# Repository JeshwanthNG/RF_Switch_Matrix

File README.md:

# RF_Switch_Matrix
Project Implementing RF Switch Matrix, Includes hardware, software and PC application 

## Getting Started

### Prerequisites

- **Windows** for GUI development
- **Visual Studio 2022** with .NET desktop development workload
- **STM32CubeIDE** or **STM32CubeMX** with preferred IDE
- **STM32F439ZI** development board

### Clone the repository

```bash
git clone https://github.com/JeshwanthNG/RF_Switch_Matrix.git
cd RF_Switch_Matrix

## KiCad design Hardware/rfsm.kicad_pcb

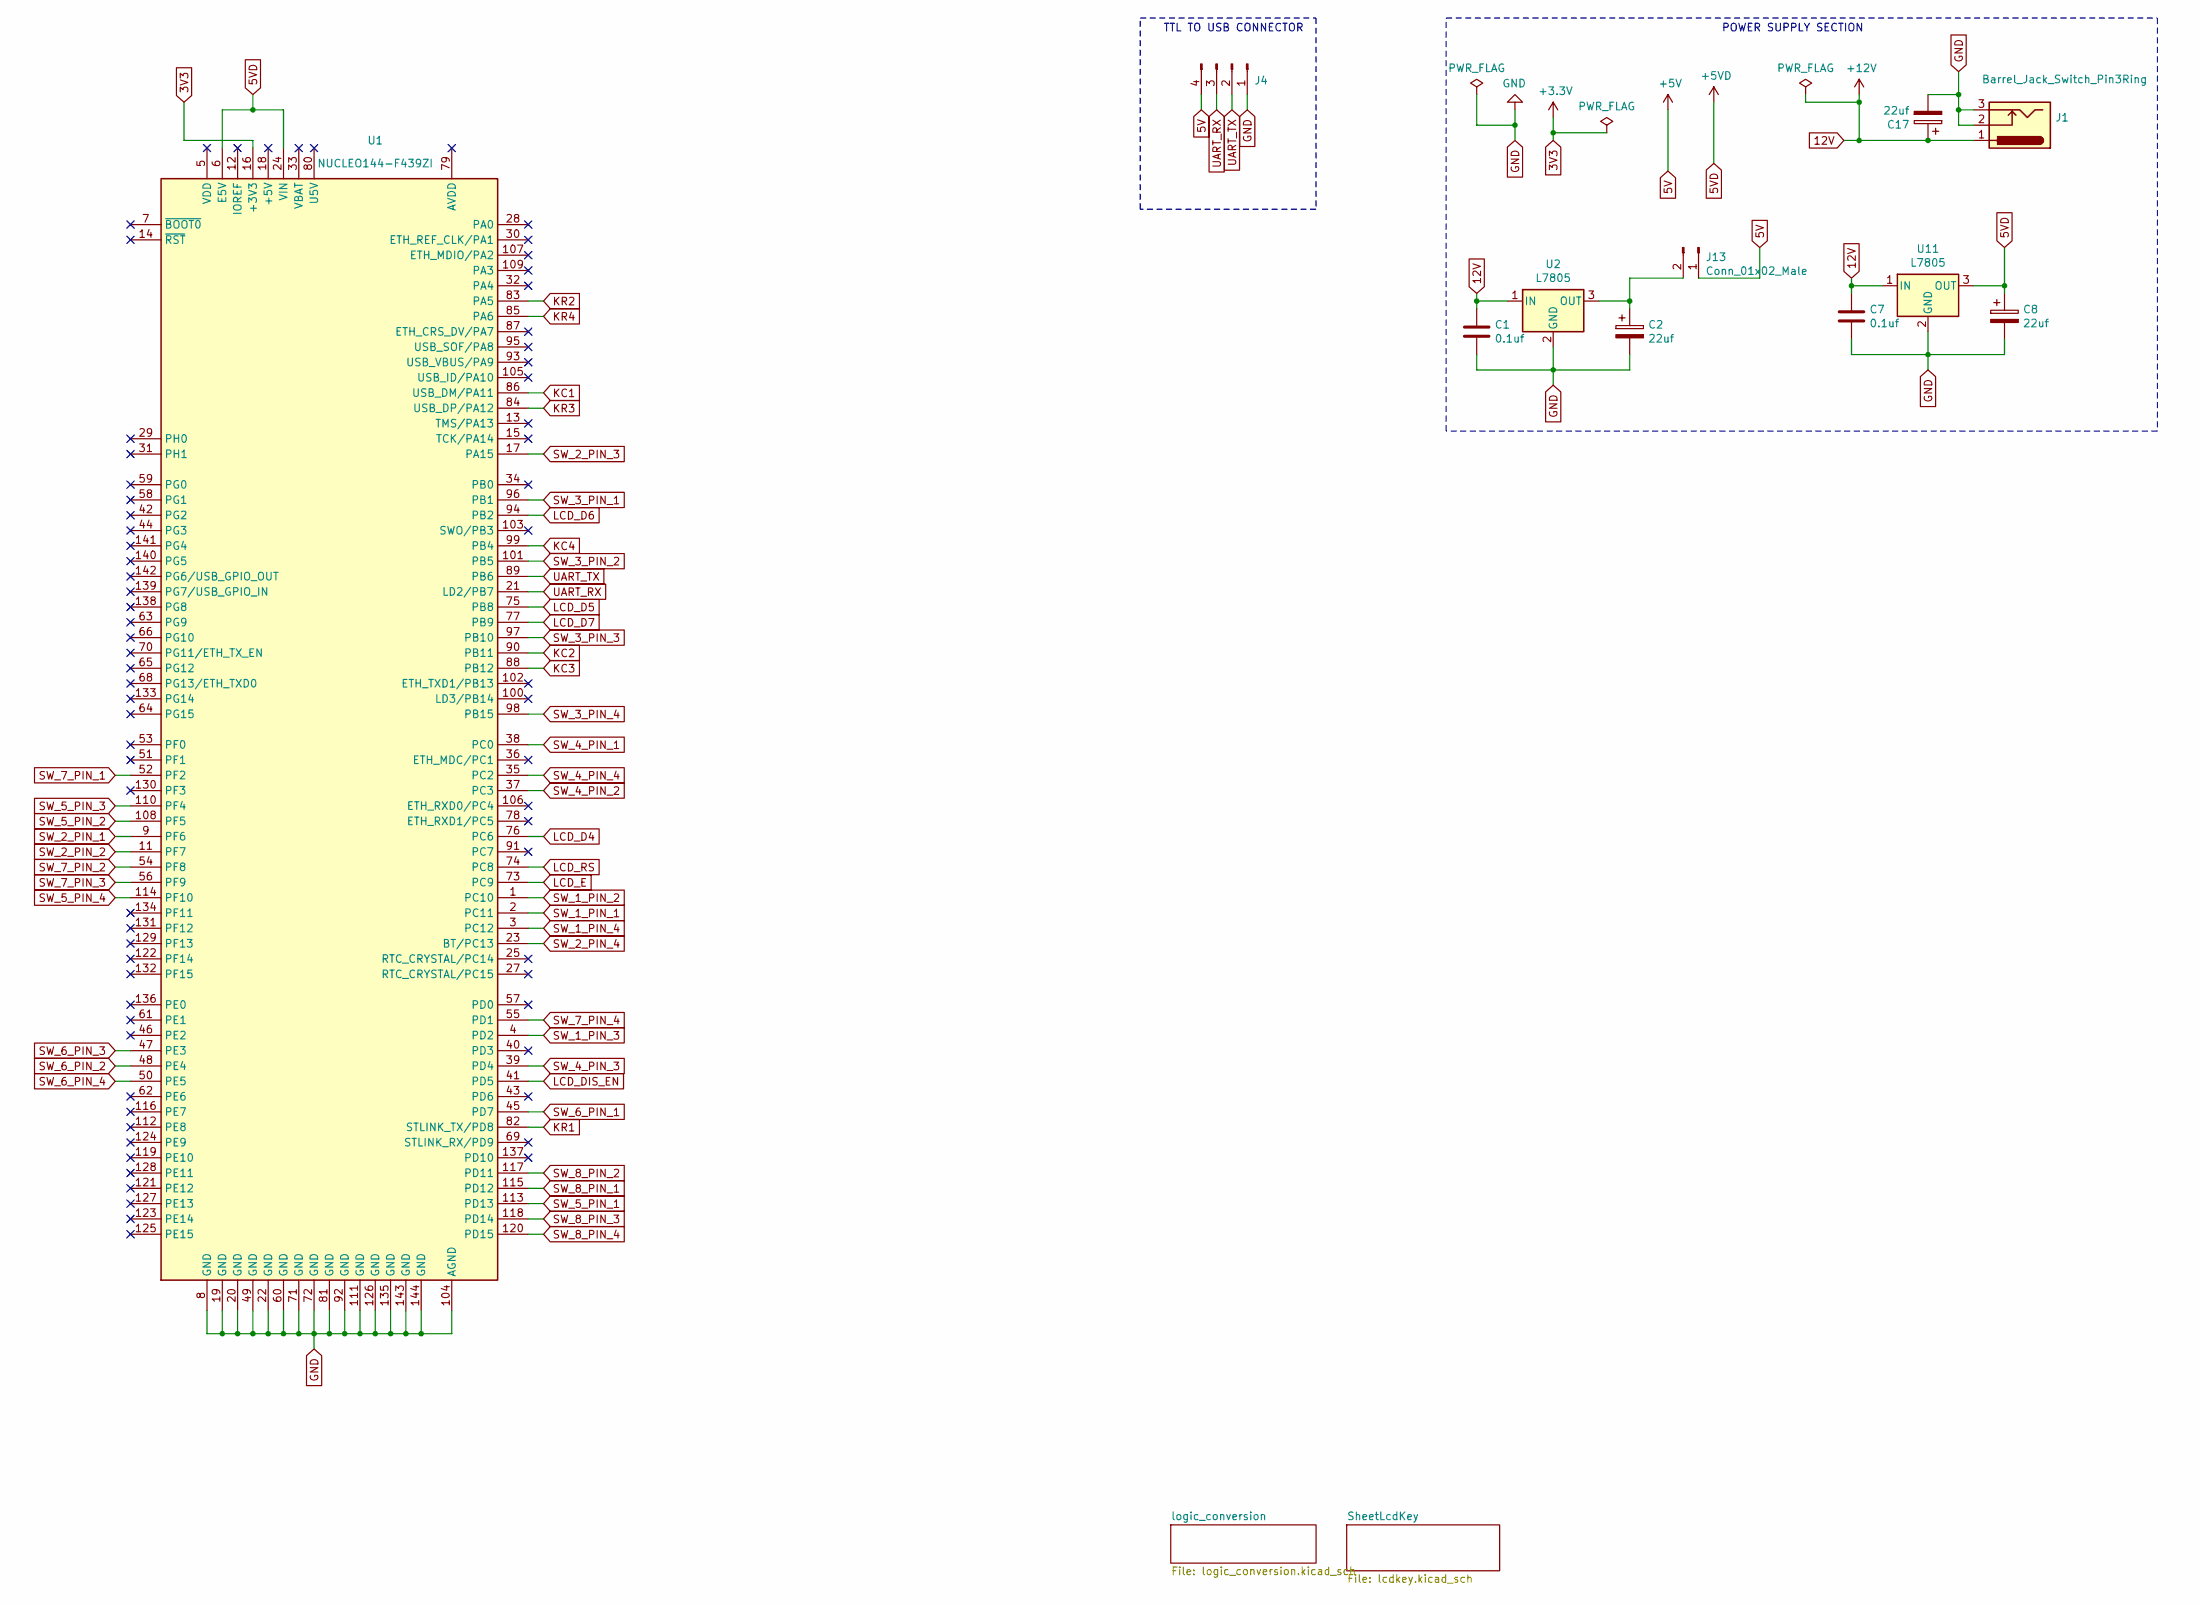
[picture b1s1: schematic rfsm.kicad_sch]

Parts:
C1, C7: 0.1uf; C_0805_2012Metric_Pad1.18x1.45mm_HandSolder
C2, C8, C17: 22uf; CP_EIA-2012-12_Kemet-R_Pad1.30x1.05mm_HandSolder
J1: Barrel_Jack_Switch_Pin3Ring; BarrelJack_Horizontal
J4: Conn_01x04_Male; JST_EH_B4B-EH-A_1x04_P2.50mm_Vertical
J13: Conn_01x02_Male; PinSocket_1x02_P2.54mm_Vertical
U1: NUCLEO144-F439ZI; ST_Morpho_Connector_144_STLink
U2, U11: L7805; TO-220-3_Vertical

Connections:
3V3: U1.16 (+3V3); also elsewhere on the board
5V: J4.4, J13.1; also elsewhere on the board
5VD: C8.1, U1.6 (E5V), U1.24 (VIN), U11.3 (OUT)
12V: C1.1, C7.1, C17.1, J1.1, U2.1 (IN), U11.1 (IN); also elsewhere on the board
GND: C1.2, C2.2, C7.2, C8.2, C17.2, J1.2, J1.3, J4.1, U1.8 (GND), U1.19 (GND), U1.20 (GND), U1.22 (GND), U1.49 (GND), U1.60 (GND), U1.71 (GND), U1.72 (GND), U1.81 (GND), U1.92 (GND), U1.104 (AGND), U1.111 (GND), U1.126 (GND), U1.135 (GND), U1.143 (GND), U1.144 (GND), U2.2 (GND), U11.2 (GND); also elsewhere on the board
KC1: U1.86 (USB_DM/PA11); also elsewhere on the board
KC2: U1.90 (PB11); also elsewhere on the board
KC3: U1.88 (PB12); also elsewhere on the board
KC4: U1.99 (PB4); also elsewhere on the board
KR1: U1.82 (STLINK_TX/PD8); also elsewhere on the board
KR2: U1.83 (PA5); also elsewhere on the board
KR3: U1.84 (USB_DP/PA12); also elsewhere on the board
KR4: U1.85 (PA6); also elsewhere on the board
LCD_D4: U1.76 (PC6); also elsewhere on the board
LCD_D5: U1.75 (PB8); also elsewhere on the board
LCD_D6: U1.94 (PB2); also elsewhere on the board
LCD_D7: U1.77 (PB9); also elsewhere on the board
LCD_DIS_EN: U1.41 (PD5); also elsewhere on the board
LCD_E: U1.73 (PC9); also elsewhere on the board
LCD_RS: U1.74 (PC8); also elsewhere on the board
unnamed: C2.1, J13.2, U2.3 (OUT)
SW_1_PIN_1: U1.2 (PC11); also elsewhere on the board
SW_1_PIN_2: U1.1 (PC10); also elsewhere on the board
SW_1_PIN_3: U1.4 (PD2); also elsewhere on the board
SW_1_PIN_4: U1.3 (PC12); also elsewhere on the board
SW_2_PIN_1: U1.9 (PF6); also elsewhere on the board
SW_2_PIN_2: U1.11 (PF7); also elsewhere on the board
SW_2_PIN_3: U1.17 (PA15); also elsewhere on the board
SW_2_PIN_4: U1.23 (BT/PC13); also elsewhere on the board
SW_3_PIN_1: U1.96 (PB1); also elsewhere on the board
SW_3_PIN_2: U1.101 (PB5); also elsewhere on the board
SW_3_PIN_3: U1.97 (PB10); also elsewhere on the board
SW_3_PIN_4: U1.98 (PB15); also elsewhere on the board
SW_4_PIN_1: U1.38 (PC0); also elsewhere on the board
SW_4_PIN_2: U1.37 (PC3); also elsewhere on the board
SW_4_PIN_3: U1.39 (PD4); also elsewhere on the board
SW_4_PIN_4: U1.35 (PC2); also elsewhere on the board
SW_5_PIN_1: U1.113 (PD13); also elsewhere on the board
SW_5_PIN_2: U1.108 (PF5); also elsewhere on the board
SW_5_PIN_3: U1.110 (PF4); also elsewhere on the board
SW_5_PIN_4: U1.114 (PF10); also elsewhere on the board
SW_6_PIN_1: U1.45 (PD7); also elsewhere on the board
SW_6_PIN_2: U1.48 (PE4); also elsewhere on the board
SW_6_PIN_3: U1.47 (PE3); also elsewhere on the board
SW_6_PIN_4: U1.50 (PE5); also elsewhere on the board
SW_7_PIN_1: U1.52 (PF2); also elsewhere on the board
SW_7_PIN_2: U1.54 (PF8); also elsewhere on the board
SW_7_PIN_3: U1.56 (PF9); also elsewhere on the board
SW_7_PIN_4: U1.55 (PD1); also elsewhere on the board
SW_8_PIN_1: U1.115 (PD12); also elsewhere on the board
SW_8_PIN_2: U1.117 (PD11); also elsewhere on the board
SW_8_PIN_3: U1.118 (PD14); also elsewhere on the board
SW_8_PIN_4: U1.120 (PD15); also elsewhere on the board
UART_RX: J4.3, U1.21 (LD2/PB7)
UART_TX: J4.2, U1.89 (PB6)

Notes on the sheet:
POWER SUPPLY SECTION
TTL TO USB CONNECTOR

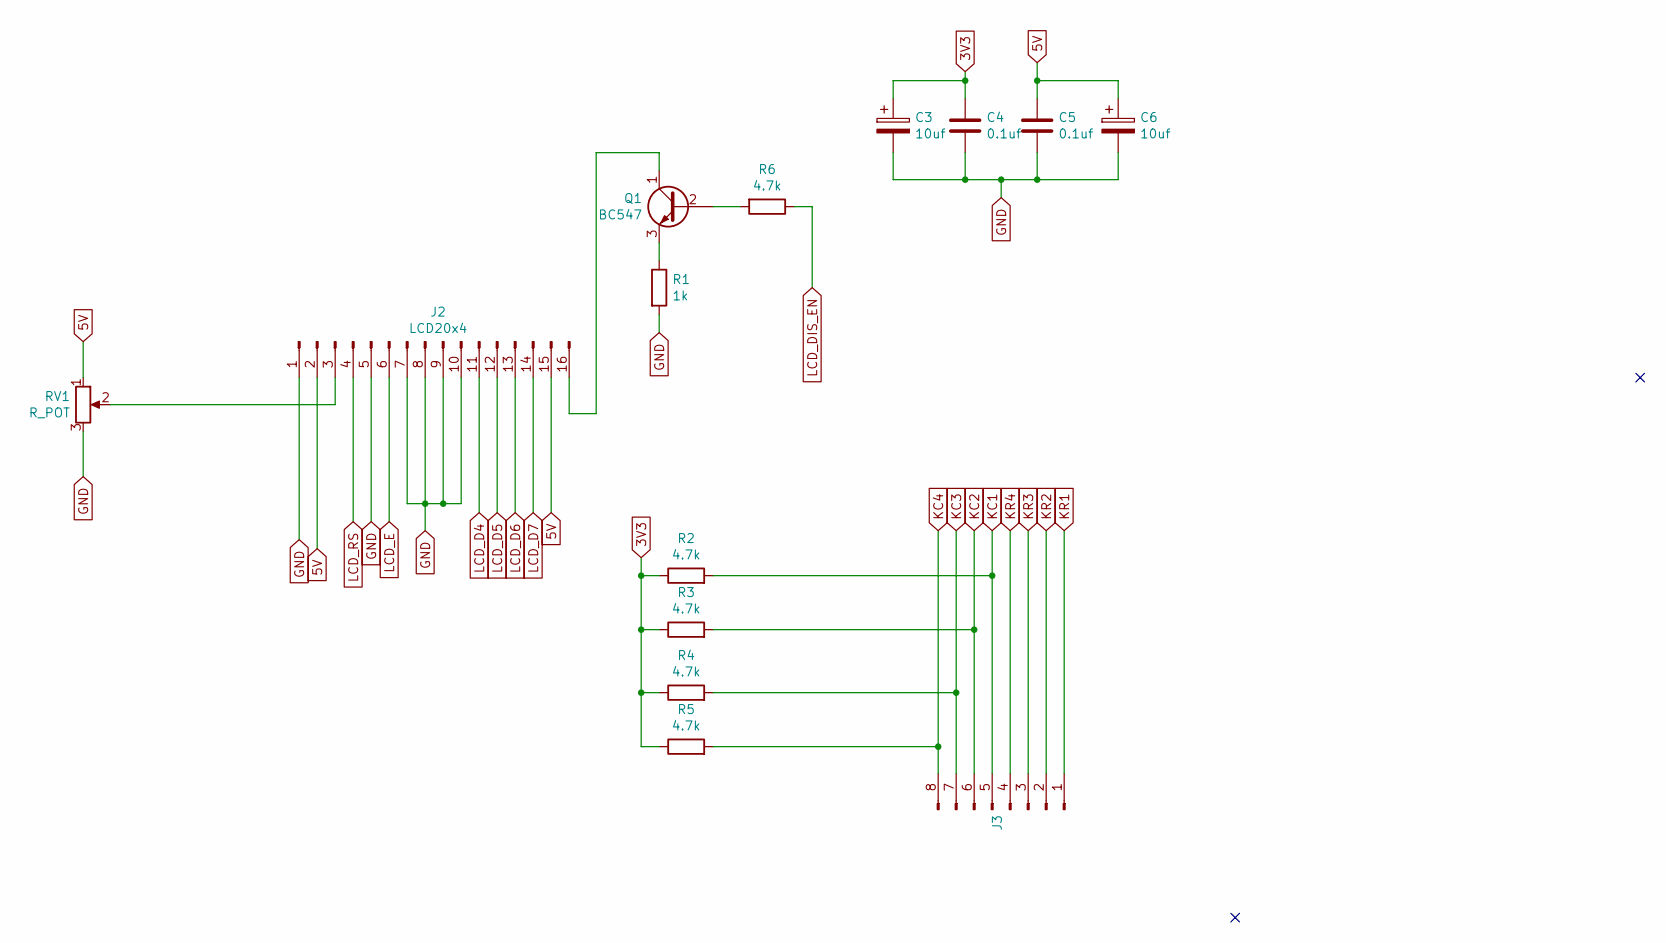
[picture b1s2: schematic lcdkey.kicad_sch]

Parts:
C3, C6: 10uf; CP_EIA-2012-12_Kemet-R_Pad1.30x1.05mm_HandSolder
C4, C5: 0.1uf; C_0805_2012Metric_Pad1.18x1.45mm_HandSolder
J2: LCD20x4; PinSocket_1x16_P2.54mm_Vertical
J3: Conn_01x08_Male; PinSocket_1x08_P2.54mm_Vertical
Q1: BC547; SOT-23
R1: 1k; R_0805_2012Metric_Pad1.20x1.40mm_HandSolder
R2, R3, R4, R5, R6: 4.7k; R_0805_2012Metric_Pad1.20x1.40mm_HandSolder
RV1: R_POT; Potentiometer_Bourns_3296W_Vertical

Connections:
3V3: C3.1, C4.1, R2.1, R3.1, R4.1, R5.1; also elsewhere on the board
5V: C5.1, C6.1, J2.2, J2.15, RV1.1; also elsewhere on the board
GND: C3.2, C4.2, C5.2, C6.2, J2.1, J2.5, J2.7, J2.8, J2.9, J2.10, R1.2, RV1.3; also elsewhere on the board
KC1: J3.5, R2.2; also elsewhere on the board
KC2: J3.6, R3.2; also elsewhere on the board
KC3: J3.7, R4.2; also elsewhere on the board
KC4: J3.8, R5.2; also elsewhere on the board
KR1: J3.1; also elsewhere on the board
KR2: J3.2; also elsewhere on the board
KR3: J3.3; also elsewhere on the board
KR4: J3.4; also elsewhere on the board
LCD_D4: J2.11; also elsewhere on the board
LCD_D5: J2.12; also elsewhere on the board
LCD_D6: J2.13; also elsewhere on the board
LCD_D7: J2.14; also elsewhere on the board
LCD_DIS_EN: R6.1; also elsewhere on the board
LCD_E: J2.6; also elsewhere on the board
LCD_RS: J2.4; also elsewhere on the board
unnamed: J2.3, RV1.2
unnamed: J2.16, Q1.1 (C)
unnamed: Q1.2 (B), R6.2
unnamed: Q1.3 (E), R1.1

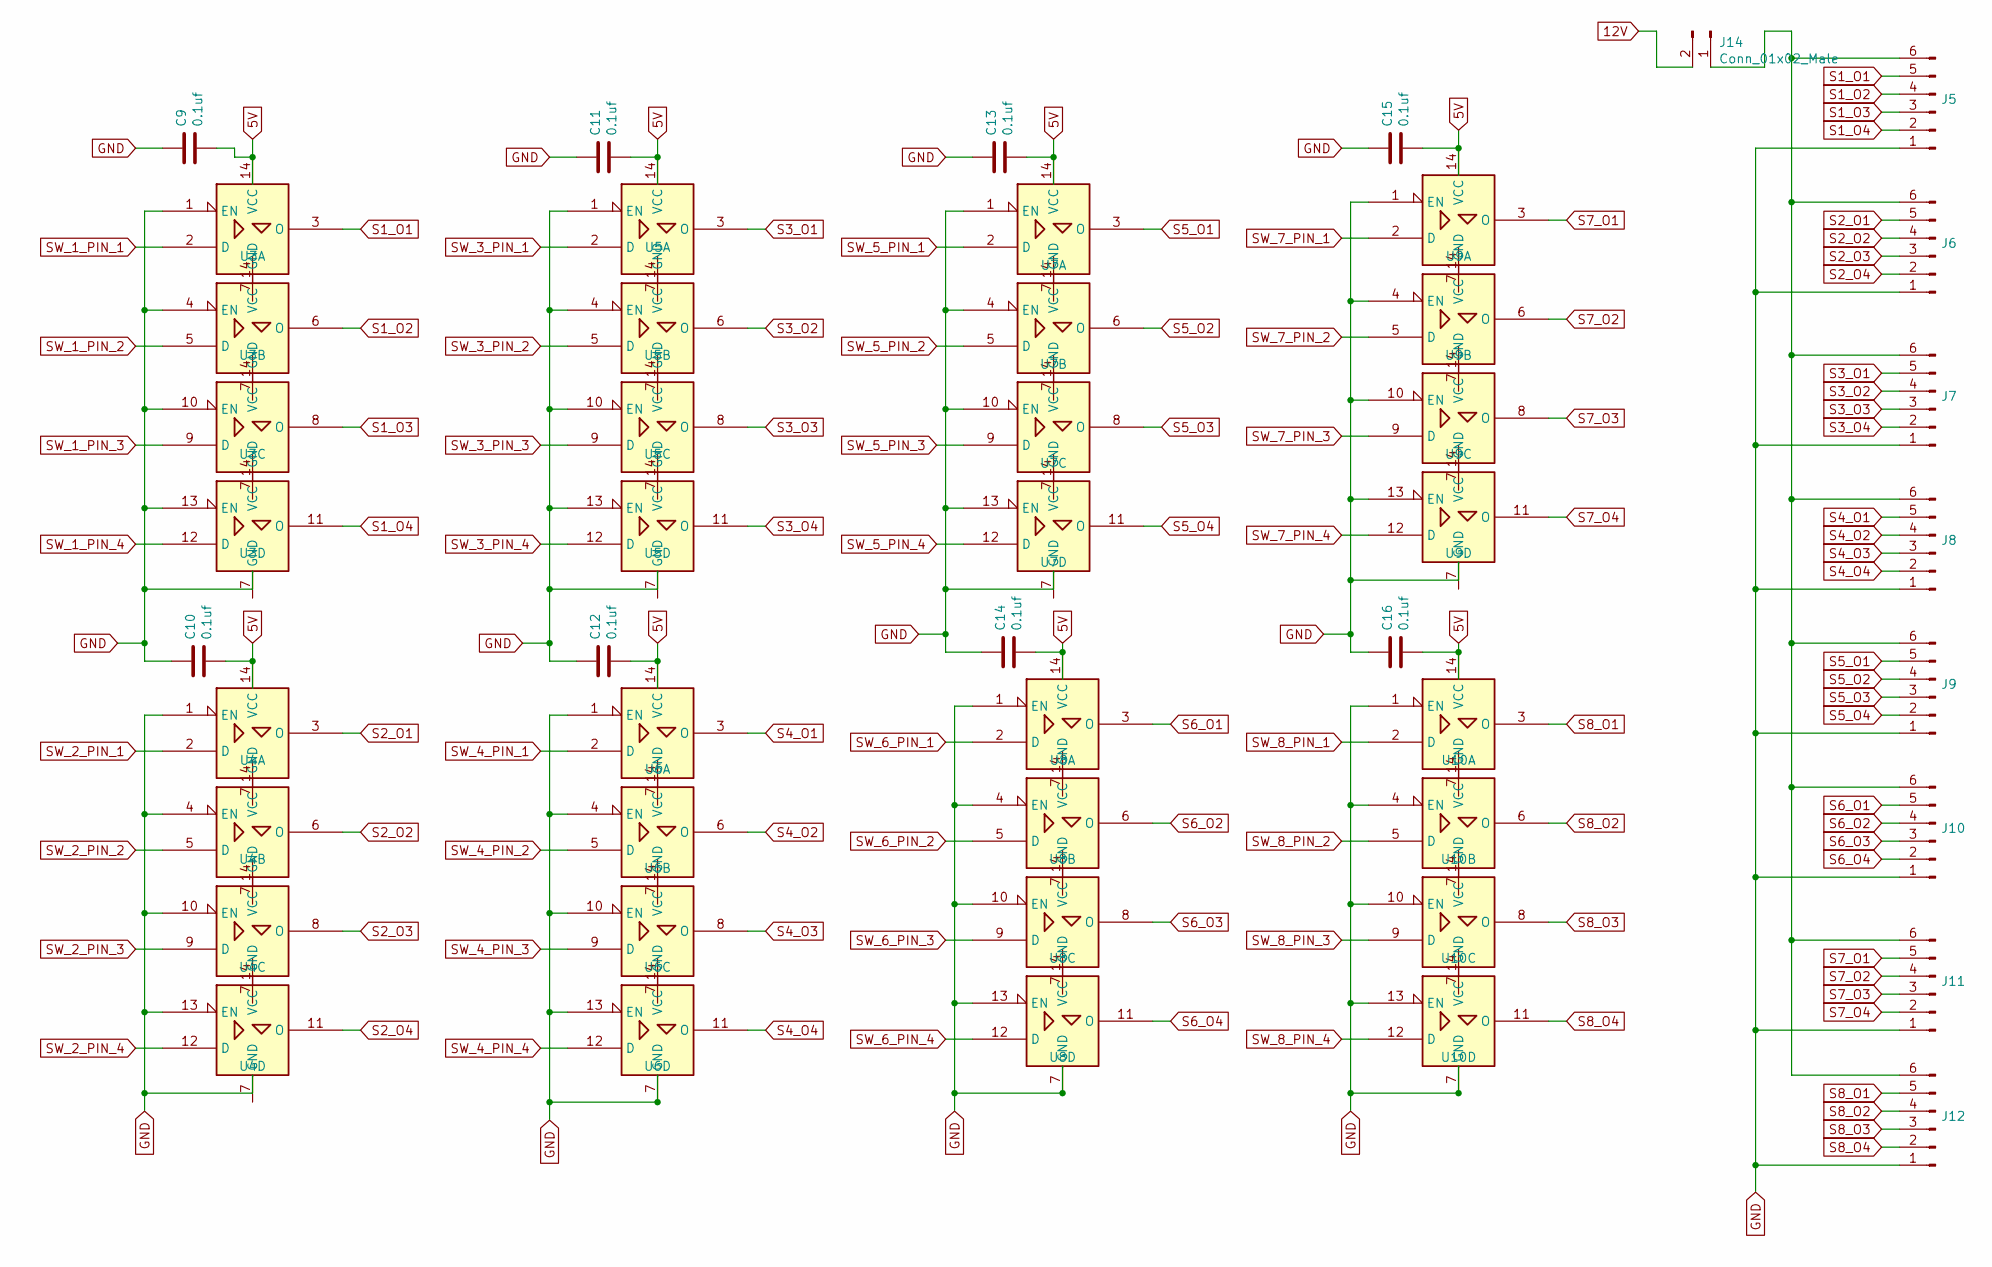
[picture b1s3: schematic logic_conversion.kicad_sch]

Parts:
C9, C10, C11, C12, C13, C14, C15, C16: 0.1uf; C_0805_2012Metric_Pad1.18x1.45mm_HandSolder
J5, J6, J7, J8, J9, J10, J11, J12: Conn_01x06_Male; JST_EH_B6B-EH-A_1x06_P2.50mm_Vertical
J14: Conn_01x02_Male; PinSocket_1x02_P2.54mm_Vertical
U3, U4, U5, U6, U7, U8, U9, U10: 74125; DIP-14_W7.62mm_Socket

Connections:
5V: C9.2, C10.2, C11.2, C12.2, C13.2, C14.2, C15.2, C16.2, U3.14 (VCC), U4.14 (VCC), U5.14 (VCC), U6.14 (VCC), U7.14 (VCC), U8.14 (VCC), U9.14 (VCC), U10.14 (VCC); also elsewhere on the board
12V: J14.2; also elsewhere on the board
GND: C9.1, C10.1, C11.1, C12.1, C13.1, C14.1, C15.1, C16.1, J5.1, J6.1, J7.1, J8.1, J9.1, J10.1, J11.1, J12.1, U3.1 (EN), U3.4 (EN), U3.7 (GND), U3.10 (EN), U3.13 (EN), U4.1 (EN), U4.4 (EN), U4.7 (GND), U4.10 (EN), U4.13 (EN), U5.1 (EN), U5.4 (EN), U5.7 (GND), U5.10 (EN), U5.13 (EN), U6.1 (EN), U6.4 (EN), U6.7 (GND), U6.10 (EN), U6.13 (EN), U7.1 (EN), U7.4 (EN), U7.7 (GND), U7.10 (EN), U7.13 (EN), U8.1 (EN), U8.4 (EN), U8.7 (GND), U8.10 (EN), U8.13 (EN), U9.1 (EN), U9.4 (EN), U9.7 (GND), U9.10 (EN), U9.13 (EN), U10.1 (EN), U10.4 (EN), U10.7 (GND), U10.10 (EN), U10.13 (EN); also elsewhere on the board
unnamed: J5.6, J6.6, J7.6, J8.6, J9.6, J10.6, J11.6, J12.6, J14.1
S1_O1: J5.5, U3.3 (O)
S1_O2: J5.4, U3.6 (O)
S1_O3: J5.3, U3.8 (O)
S1_O4: J5.2, U3.11 (O)
S2_O1: J6.5, U4.3 (O)
S2_O2: J6.4, U4.6 (O)
S2_O3: J6.3, U4.8 (O)
S2_O4: J6.2, U4.11 (O)
S3_O1: J7.5, U5.3 (O)
S3_O2: J7.4, U5.6 (O)
S3_O3: J7.3, U5.8 (O)
S3_O4: J7.2, U5.11 (O)
S4_O1: J8.5, U6.3 (O)
S4_O2: J8.4, U6.6 (O)
S4_O3: J8.3, U6.8 (O)
S4_O4: J8.2, U6.11 (O)
S5_O1: J9.5, U7.3 (O)
S5_O2: J9.4, U7.6 (O)
S5_O3: J9.3, U7.8 (O)
S5_O4: J9.2, U7.11 (O)
S6_O1: J10.5, U8.3 (O)
S6_O2: J10.4, U8.6 (O)
S6_O3: J10.3, U8.8 (O)
S6_O4: J10.2, U8.11 (O)
S7_O1: J11.5, U9.3 (O)
S7_O2: J11.4, U9.6 (O)
S7_O3: J11.3, U9.8 (O)
S7_O4: J11.2, U9.11 (O)
S8_O1: J12.5, U10.3 (O)
S8_O2: J12.4, U10.6 (O)
S8_O3: J12.3, U10.8 (O)
S8_O4: J12.2, U10.11 (O)
SW_1_PIN_1: U3.2 (D); also elsewhere on the board
SW_1_PIN_2: U3.5 (D); also elsewhere on the board
SW_1_PIN_3: U3.9 (D); also elsewhere on the board
SW_1_PIN_4: U3.12 (D); also elsewhere on the board
SW_2_PIN_1: U4.2 (D); also elsewhere on the board
SW_2_PIN_2: U4.5 (D); also elsewhere on the board
SW_2_PIN_3: U4.9 (D); also elsewhere on the board
SW_2_PIN_4: U4.12 (D); also elsewhere on the board
SW_3_PIN_1: U5.2 (D); also elsewhere on the board
SW_3_PIN_2: U5.5 (D); also elsewhere on the board
SW_3_PIN_3: U5.9 (D); also elsewhere on the board
SW_3_PIN_4: U5.12 (D); also elsewhere on the board
SW_4_PIN_1: U6.2 (D); also elsewhere on the board
SW_4_PIN_2: U6.5 (D); also elsewhere on the board
SW_4_PIN_3: U6.9 (D); also elsewhere on the board
SW_4_PIN_4: U6.12 (D); also elsewhere on the board
SW_5_PIN_1: U7.2 (D); also elsewhere on the board
SW_5_PIN_2: U7.5 (D); also elsewhere on the board
SW_5_PIN_3: U7.9 (D); also elsewhere on the board
SW_5_PIN_4: U7.12 (D); also elsewhere on the board
SW_6_PIN_1: U8.2 (D); also elsewhere on the board
SW_6_PIN_2: U8.5 (D); also elsewhere on the board
SW_6_PIN_3: U8.9 (D); also elsewhere on the board
SW_6_PIN_4: U8.12 (D); also elsewhere on the board
SW_7_PIN_1: U9.2 (D); also elsewhere on the board
SW_7_PIN_2: U9.5 (D); also elsewhere on the board
SW_7_PIN_3: U9.9 (D); also elsewhere on the board
SW_7_PIN_4: U9.12 (D); also elsewhere on the board
SW_8_PIN_1: U10.2 (D); also elsewhere on the board
SW_8_PIN_2: U10.5 (D); also elsewhere on the board
SW_8_PIN_3: U10.9 (D); also elsewhere on the board
SW_8_PIN_4: U10.12 (D); also elsewhere on the board

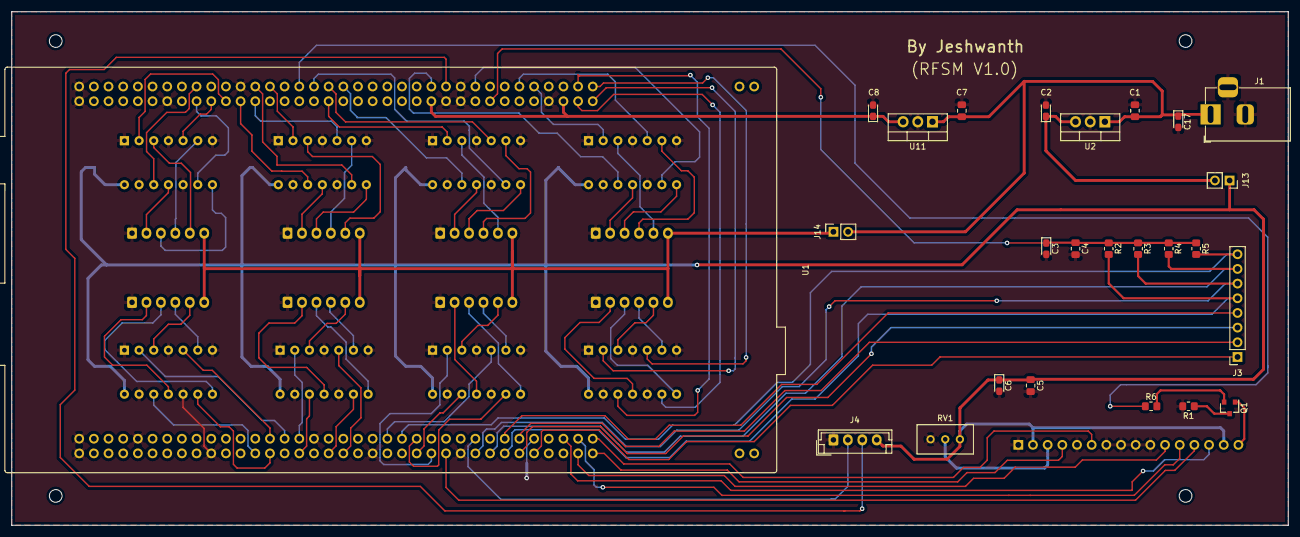
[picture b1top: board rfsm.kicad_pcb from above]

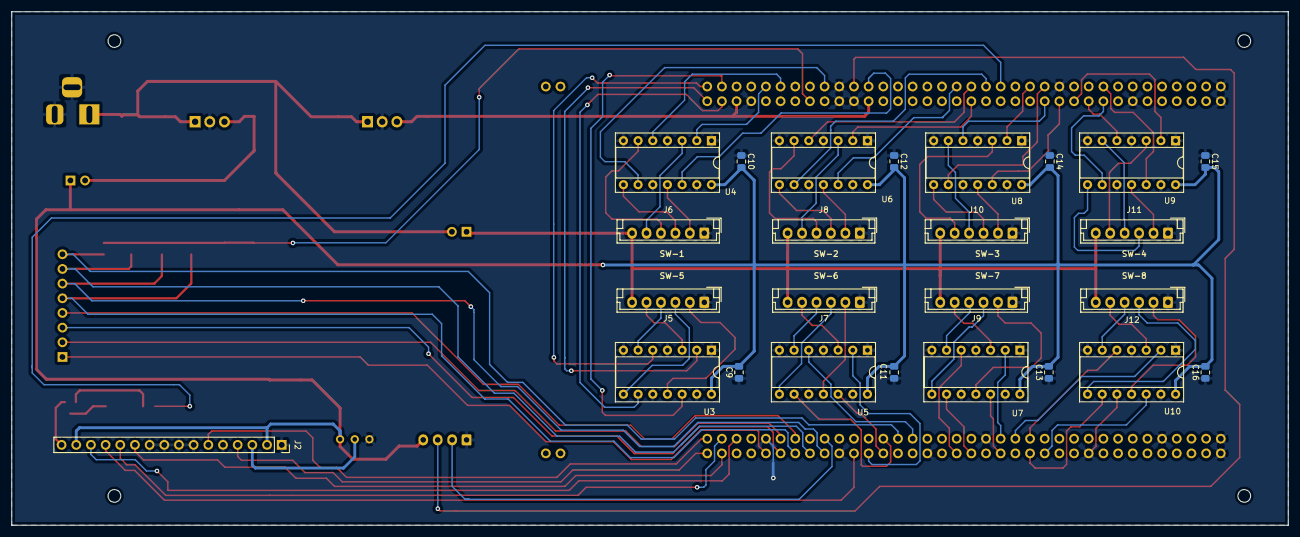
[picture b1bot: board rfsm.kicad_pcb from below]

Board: 2 copper layers, 221.0 x 88.9 mm, 50 parts (25 on the bottom side), 92 nets.

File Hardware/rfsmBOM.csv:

"Id";"Designator";"Package";"Quantity";"Designation";"Supplier and ref";
1;"J14,J13";"PinSocket_1x02_P2.54mm_Vertical";2;"Conn_01x02_Male";;;
2;"U1";"ST_Morpho_Connector_144_STLink";1;"NUCLEO144-F439ZI";;;
3;"C15,C16,C14,C13,C12,C11,C10,C9,C1,C4,C5,C7";"C_0805_2012Metric_Pad1.18x1.45mm_HandSolder";12;"0.1uf";;;
4;"C17,C2,C8";"CP_EIA-2012-12_Kemet-R_Pad1.30x1.05mm_HandSolder";3;"22uf";;;
5;"REF**,REF**,REF**,REF**";"MountingHole_2.2mm_M2";4;"MountingHole_2.2mm_M2";;;
6;"U9,U3,U4,U5,U6,U7,U8,U10";"DIP-14_W7.62mm_Socket";8;"74125";;;
7;"C3,C6";"CP_EIA-2012-12_Kemet-R_Pad1.30x1.05mm_HandSolder";2;"10uf";;;
8;"J1";"BarrelJack_Horizontal";1;"Barrel_Jack_Switch_Pin3Ring";;;
9;"J2";"PinSocket_1x16_P2.54mm_Vertical";1;"LCD20x4";;;
10;"J3";"PinSocket_1x08_P2.54mm_Vertical";1;"Conn_01x08_Male";;;
11;"J4";"JST_EH_B4B-EH-A_1x04_P2.50mm_Vertical";1;"Conn_01x04_Male";;;
12;"J5,J6,J7,J8,J9,J10,J11,J12";"JST_EH_B6B-EH-A_1x06_P2.50mm_Vertical";8;"Conn_01x06_Male";;;
13;"Q1";"SOT-23";1;"BC547";;;
14;"R1";"R_0805_2012Metric_Pad1.20x1.40mm_HandSolder";1;"1k";;;
15;"R2,R3,R4,R5,R6";"R_0805_2012Metric_Pad1.20x1.40mm_HandSolder";5;"4.7k";;;
16;"RV1";"Potentiometer_Bourns_3296W_Vertical";1;"R_POT";;;
17;"U2,U11";"TO-220-3_Vertical";2;"L7805";;;

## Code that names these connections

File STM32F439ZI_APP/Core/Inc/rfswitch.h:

/*
 * rfswitch.h
 *
 *  Created on: Nov 29, 2020
 *      Author: 600034585
 */

#ifndef INC_RFSWITCH_H_
#define INC_RFSWITCH_H_

/*
 GPIO MAPPING FOR SWITCHES
    INPUT             OUTPUT
 -----------       -----------
 Switch1 PC11       Switch5 PB1
 	     PC10       	    PB2
 	     PD2      	        PB3
 	     PC12       	    PB4

 Switch2           Switch6
         PB5               PB5
         PB6               PB6
         PB7               PB7
         PB8               PB8

 Switch3           Switch7
 	 	 PB9       	 	   PB9
 	 	 PB10      	 	   PB10
 	 	 PB11      	 	   PB11
 	 	 PB12      	 	   PB12

 Switch4           Switch8
 	 	 PC1       	 	   PC1
 	 	 PC2       	 	   PC2
 	 	 PC3       	 	   PC3
 	 	 PC4       	 	   PC4

 *
 */

#define MAX_IN_OUT_SWITCHES (4)

//Switch 1 GPIO
#define SW1_PIN1_PORT	GPIOC
#define SW1_PIN1_PIN  	GPIO_PIN_11
#define SW1_PIN2_PORT	GPIOC
#define SW1_PIN2_PIN  	GPIO_PIN_10
#define SW1_PIN3_PORT	GPIOD
#define SW1_PIN3_PIN  	GPIO_PIN_2
#define SW1_PIN4_PORT	GPIOC
#define SW1_PIN4_PIN  	GPIO_PIN_12
//Switch 2 GPIO
#define SW2_PIN1_PORT	GPIOF
#define SW2_PIN1_PIN  	GPIO_PIN_6
#define SW2_PIN2_PORT	GPIOF
#define SW2_PIN2_PIN  	GPIO_PIN_7
#define SW2_PIN3_PORT	GPIOA
#define SW2_PIN3_PIN  	GPIO_PIN_15
#define SW2_PIN4_PORT	GPIOC
#define SW2_PIN4_PIN  	GPIO_PIN_13
//Switch 3 GPIO
#define SW3_PIN1_PORT	GPIOA
#define SW3_PIN1_PIN  	GPIO_PIN_0
#define SW3_PIN2_PORT	GPIOA
#define SW3_PIN2_PIN  	GPIO_PIN_4
#define SW3_PIN3_PORT	GPIOB
#define SW3_PIN3_PIN  	GPIO_PIN_0
#define SW3_PIN4_PORT	GPIOC
#define SW3_PIN4_PIN  	GPIO_PIN_2
//Switch 4 GPIO
#define SW4_PIN1_PORT	GPIOC
#define SW4_PIN1_PIN  	GPIO_PIN_0
#define SW4_PIN2_PORT	GPIOC
#define SW4_PIN2_PIN  	GPIO_PIN_3
#define SW4_PIN3_PORT	GPIOD
#define SW4_PIN3_PIN  	GPIO_PIN_3
#define SW4_PIN4_PORT	GPIOD
#define SW4_PIN4_PIN  	GPIO_PIN_7




typedef struct STRUCT_RF_SWITCH
{
	uint8_t input_switches;
	uint8_t output_switches;
}STRUCT_RF_SWITCH;

void SwitchMatrixInitialize(void);
uint8_t SwitchSetInput(uint8_t inputSwNum, uint8_t outputSwNum);
uint8_t SwitchSetOutput(uint8_t outputSwNum, uint8_t inputSwNum);
uint8_t SwitchReadInput(uint8_t inputSwNum, uint8_t* outputSwNum);
uint8_t SwitchReadOuput(uint8_t outputSwNum, uint8_t* inputSwNum);
void SwitchReadAllSwitches(STRUCT_RF_SWITCH* Inputs);



#endif /* INC_RFSWITCH_H_ */

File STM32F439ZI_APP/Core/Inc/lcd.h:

/*
 * lcd.h
 *
 *  Created on: 27-Nov-2020
 *      Author: 600034585
 */

#ifndef INC_LCD_H_
#define INC_LCD_H_



#define LCD_RS_PORT (GPIOC)
#define LCD_RS_PIN  (GPIO_PIN_8)

#define LCD_EN_PORT (GPIOC)
#define LCD_EN_PIN  (GPIO_PIN_9)

#define LCD_D4_PORT (GPIOC)
#define LCD_D4_PIN  (GPIO_PIN_6)

#define LCD_D5_PORT (GPIOB)
#define LCD_D5_PIN  (GPIO_PIN_8)

#define LCD_D6_PORT (GPIOB)
#define LCD_D6_PIN  (GPIO_PIN_2)

#define LCD_D7_PORT (GPIOB)
#define LCD_D7_PIN  (GPIO_PIN_9)


void LcdPutString(uint8_t x, uint8_t y, const char *strPtr);
void LcdPutByte(uint8_t x, uint8_t y, char byte);
void LcdClear(void);
void LcdInitialize(void);

#endif /* INC_LCD_H_ */

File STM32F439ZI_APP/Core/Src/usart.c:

/**
  ******************************************************************************
  * File Name          : USART.c
  * Description        : This file provides code for the configuration
  *                      of the USART instances.
  ******************************************************************************
  * @attention
  *
  * <h2><center>&copy; Copyright (c) 2020 STMicroelectronics.
  * All rights reserved.</center></h2>
  *
  * This software component is licensed by ST under BSD 3-Clause license,
  * the "License"; You may not use this file except in compliance with the
  * License. You may obtain a copy of the License at:
  *                        opensource.org/licenses/BSD-3-Clause
  *
  ******************************************************************************
  */

/* Includes ------------------------------------------------------------------*/
#include "usart.h"

#define USE_RS485


UART_HandleTypeDef huart1;

#ifdef USE_RS485
UART_HandleTypeDef huart2;
#endif

/* USART1 init function */

void MX_USART1_UART_Init(void)
{

  huart1.Instance = USART1;
  huart1.Init.BaudRate = 19200;//115200;
  huart1.Init.WordLength = UART_WORDLENGTH_8B;
  huart1.Init.StopBits = UART_STOPBITS_1;
  huart1.Init.Parity = UART_PARITY_NONE;
  huart1.Init.Mode = UART_MODE_TX_RX;
  huart1.Init.HwFlowCtl = UART_HWCONTROL_NONE;
  huart1.Init.OverSampling = UART_OVERSAMPLING_16;


  if (HAL_UART_Init(&huart1) != HAL_OK)
  {
    Error_Handler();
  }
}

#ifdef USE_RS485
void MX_USART2_UART_Init(void)
{

  huart2.Instance = USART2;
  huart2.Init.BaudRate = 19200;//115200;
  huart2.Init.WordLength = UART_WORDLENGTH_8B;
  huart2.Init.StopBits = UART_STOPBITS_1;
  huart2.Init.Parity = UART_PARITY_NONE;
  huart2.Init.Mode = UART_MODE_TX_RX;
  huart2.Init.HwFlowCtl = UART_HWCONTROL_NONE;
  huart2.Init.OverSampling = UART_OVERSAMPLING_16;

  if (HAL_UART_Init(&huart2) != HAL_OK)
  {
    Error_Handler();
  }
}
#endif

void HAL_UART_MspInit(UART_HandleTypeDef* uartHandle)
{

  GPIO_InitTypeDef GPIO_InitStruct = {0};
  if(uartHandle->Instance==USART1)
  {
  /* USER CODE BEGIN USART1_MspInit 0 */

  /* USER CODE END USART1_MspInit 0 */
    /* USART1 clock enable */
    __HAL_RCC_USART1_CLK_ENABLE();

    __HAL_RCC_GPIOB_CLK_ENABLE();
    /**USART1 GPIO Configuration
    PB6     ------> USART1_TX
    PB7     ------> USART1_RX
    */
    GPIO_InitStruct.Pin = GPIO_PIN_6|GPIO_PIN_7;
    GPIO_InitStruct.Mode = GPIO_MODE_AF_PP;
    GPIO_InitStruct.Pull = GPIO_NOPULL;
    GPIO_InitStruct.Speed = GPIO_SPEED_FREQ_VERY_HIGH;
    GPIO_InitStruct.Alternate = GPIO_AF7_USART1;
    HAL_GPIO_Init(GPIOB, &GPIO_InitStruct);

    /* USART1 interrupt Init */
    HAL_NVIC_SetPriority(USART1_IRQn, 0, 0);
    HAL_NVIC_EnableIRQ(USART1_IRQn);
  /* USER CODE BEGIN USART1_MspInit 1 */

  /* USER CODE END USART1_MspInit 1 */
  }
#ifdef USE_RS485
  else if(uartHandle->Instance==USART2)
  {
  /* USER CODE BEGIN USART1_MspInit 0 */

  /* USER CODE END USART1_MspInit 0 */
    /* USART1 clock enable */
    __HAL_RCC_USART2_CLK_ENABLE();

    __HAL_RCC_GPIOD_CLK_ENABLE();
    /**USART1 GPIO Configuration
    PD5     ------> USART1_TX
    PD6     ------> USART1_RX
    PD4     ------> RTS
    */
    GPIO_InitStruct.Pin = GPIO_PIN_5|GPIO_PIN_6;
    GPIO_InitStruct.Mode = GPIO_MODE_AF_PP;
    GPIO_InitStruct.Pull = GPIO_NOPULL;
    GPIO_InitStruct.Speed = GPIO_SPEED_FREQ_VERY_HIGH;
    GPIO_InitStruct.Alternate = GPIO_AF7_USART1;
    HAL_GPIO_Init(GPIOB, &GPIO_InitStruct);

    GPIO_InitStruct.Pin = GPIO_PIN_4;
    GPIO_InitStruct.Mode = GPIO_MODE_OUTPUT_PP;
    GPIO_InitStruct.Pull = GPIO_PULLUP;
    GPIO_InitStruct.Speed = GPIO_SPEED_FREQ_LOW;
    HAL_GPIO_Init(GPIOD, &GPIO_InitStruct);

    /* USART1 interrupt Init */
    HAL_NVIC_SetPriority(USART2_IRQn, 0, 0);
    HAL_NVIC_EnableIRQ(USART2_IRQn);
  /* USER CODE BEGIN USART1_MspInit 1 */

  /* USER CODE END USART1_MspInit 1 */
  }
#endif
  else
  {

  }
}

void HAL_UART_MspDeInit(UART_HandleTypeDef* uartHandle)
{
  if(uartHandle->Instance==USART1)
  {
  /* USER CODE BEGIN USART1_MspDeInit 0 */

  /* USER CODE END USART1_MspDeInit 0 */
    /* Peripheral clock disable */
    __HAL_RCC_USART1_CLK_DISABLE();

    /**USART1 GPIO Configuration
    PB6     ------> USART1_TX
    PB7     ------> USART1_RX
    */
    HAL_GPIO_DeInit(GPIOB, GPIO_PIN_6|GPIO_PIN_7);

    /* USART1 interrupt Deinit */
    HAL_NVIC_DisableIRQ(USART1_IRQn);
  /* USER CODE BEGIN USART1_MspDeInit 1 */

  /* USER CODE END USART1_MspDeInit 1 */
  }
#ifdef USE_RS485
  else  if(uartHandle->Instance==USART2)
  {
  /* USER CODE BEGIN USART1_MspDeInit 0 */

  /* USER CODE END USART1_MspDeInit 0 */
    /* Peripheral clock disable */
    __HAL_RCC_USART2_CLK_DISABLE();

    /**USART1 GPIO Configuration
    PD5     ------> USART1_TX
    PD6     ------> USART1_RX
    PD4     ------> RTS
    */
    HAL_GPIO_DeInit(GPIOD, GPIO_PIN_4|GPIO_PIN_5|GPIO_PIN_6);

    /* USART1 interrupt Deinit */
    HAL_NVIC_DisableIRQ(USART2_IRQn);
  /* USER CODE BEGIN USART1_MspDeInit 1 */

  /* USER CODE END USART1_MspDeInit 1 */
  }
#endif
  else
  {
  }
}

/* USER CODE BEGIN 1 */

/* USER CODE END 1 */

/************************ (C) COPYRIGHT STMicroelectronics *****END OF FILE****/

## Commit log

2025-08-10 Added plantuml block diagram
2025-08-10 Added plantuml firmware architecture diagram
